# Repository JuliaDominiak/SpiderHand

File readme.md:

# SpiderHand: Supporting Arachnophobia Therapy UsingMotion-controlled Robotic Manipulator
Submitted to EAI Mobiquitous 2020

When attempting to set up the system for the first time, please consult short videos in Previews folder. It might be useful to understand the assembly details.

## Component list:
Below, we list all components necessary to successfully replicate SpiderHand manipulator. We encourage to introduce your own innovations and alter our design, yet at own risk.

**Microcontrollers and drivers**

- Adafruit Feather Huzzah ESP32   1 pcs.
- Adafruit Feather Huzzah ESP8266 5 pcs.
- ADS1015 12-Bit ADC - 4 Channel with Programmable Gain Amplifier 1 pcs.
- Adafruit 16-Channel 12-bit PWM/Servo Driver - I2C interface - PCA9685   2 pcs.

**Sensors, Servos, Devices**

- Flex Sensor 4.5"    1 pcs.
- Flex Sensor 2.2"    1 pcs.
- SparkFun Qwiic Flex Glove Controller    1 pcs.
- BendLabs 2-Axis Soft Flex Sensor    1 pcs.
- DFRobot 6 DOF Sensor - MPU6050  1 pcs.
- PowerHD HD-1501MG   3 pcs.
- PowerHD LF-20MG 1 pcs.
- Hitec HS-45HB   3 pcs.
- Shaftless Vibration Motor 10x3.4mm  5 pcs.

**Assembly Screws and Accessories**

- M2 nut  8 pcs.
- M2x8mm  11 pcs.
- M2x3mm  5 pcs.
- M3 nut  22 pcs.
- M3x6mm  8 pcs.
- M3x10mm 25 pcs.
- M3x18mm 4 pcs.
- M4 nut  2 pcs.
- M4x30mm 2 pcs.
- Aluminium horn - 20mm / 6mm 4 pcs.
- Servo extension 90cm    7 pcs.
- FeatherWing Proto - Prototyping Add-on  1 pcs.
- 10-wire Ribbon cable    5 m

**Fabric Accessories**

- Sport gloves    2 pcs.
- Elbow protector 1 pcs.
- Polyester tape (width: 2cm) 2m
- Buckles compatible with the 2cm tape    2 pcs.
- Latches 5mm 6 pcs.
- Latches 15mm    6 pcs.

## 3D printing remarks:

**Filaments used:**

1. Fiberlogy Easy PLA
2. Zortrax Z-ABS
3. Proto-paste Electrically Conductive Composite PLA
4. Fiberlogy Fiberflex 40D

**Printers used:**

1. Creality3D Ender-3
2. Zortrax M200

**Slicer:** Ultimaker Cura 4.5

Finger elements (Finger i Touch) and joints (Flex) should be reduced to 80% before printing because the elements come from the following project [https://www.thingiverse.com/thing:242639](https://www.thingiverse.com/thing:242639).

The elements from part_1 to part_10 and all the elements starting with “Finger” can be printed at your discretion using ABS or PLA. The important thing during printing is to set the lowest fill factor (in our case it is 12%) in order to relieve the construction.

The elements called “Flex” should be printed from the elastic material according to the manufacturer’s recommendations. It is suggested to use ironing on the last layer to obtain a consistent element.

The finger pads called “Touch” should be printed from the conductive material.

Before assembling according to the model, the following be embedded by heat-set insert (soldering nuts): M4: 1,2; M3: 8, 9, 24, 25, 26; M2: 1, 2, 3, 4, 5, 6, 7, 8, 12, 13

## Software remarks:

Source codes and drivers for the prototype are compatible with the Arduino IDE 1.8.12

It is necessary to install boards drivers:

1. esp32 by Espressif Systems version 1.0.2 [https://dl.espressif.com/dl/package_esp32_index.json](https://dl.espressif.com/dl/package_esp32_index.json)
2. esp8266 by ESP8266 Community version 2.1.0 [http://arduino.esp8266.com/stable/package_esp8266com_index.json](http://arduino.esp8266.com/stable/package_esp8266com_index.json)

<ins>Sensor and communication libraries used:</ins>

1. SparkFun_ADS1015_Arduino_Library
2. Adafruit_PWM_Servo_Driver_Library
3. ads_two_axis_driver
4. MPU6050
5. Adafruit_ADS1X15

**Sensor Calibration Sheet**

Auxiliary material contains a spreadsheet useful for calibrating the setup. Coefficient values for flex sensor calibration can be obtained using the Calibration.xlsx file. Please consult it for instruction on how to provide correct coefficient values to the MotorFingersElbow.ino source file.

**PCB Design**

The PCB boards were designed in EAGLE software (version 9.2.2).

## Controller assembly remarks:

Electronic components have to be sewn to the material elements.
The belt (thickness: 2cm) should be adjusted and ended with the buckles. In the middle part one shall sew one latch for each part. The other end will be attached to the sensors.

On the elbow protector 2 pairs of the 15mm latches should be attached, which will properly keep the loop and the beginning of the sensor.

Six small latches should be sewn to the glove - 5 to each vibration motor and 1 to the end of the 2-axis sensor. The remaining two bigger latches are to attach bend sensors on the fingers. In order to make the reading possible a second glove should be worn. The second option is to cut only the fingers.

Hope you’re enjoying SpiderHand!

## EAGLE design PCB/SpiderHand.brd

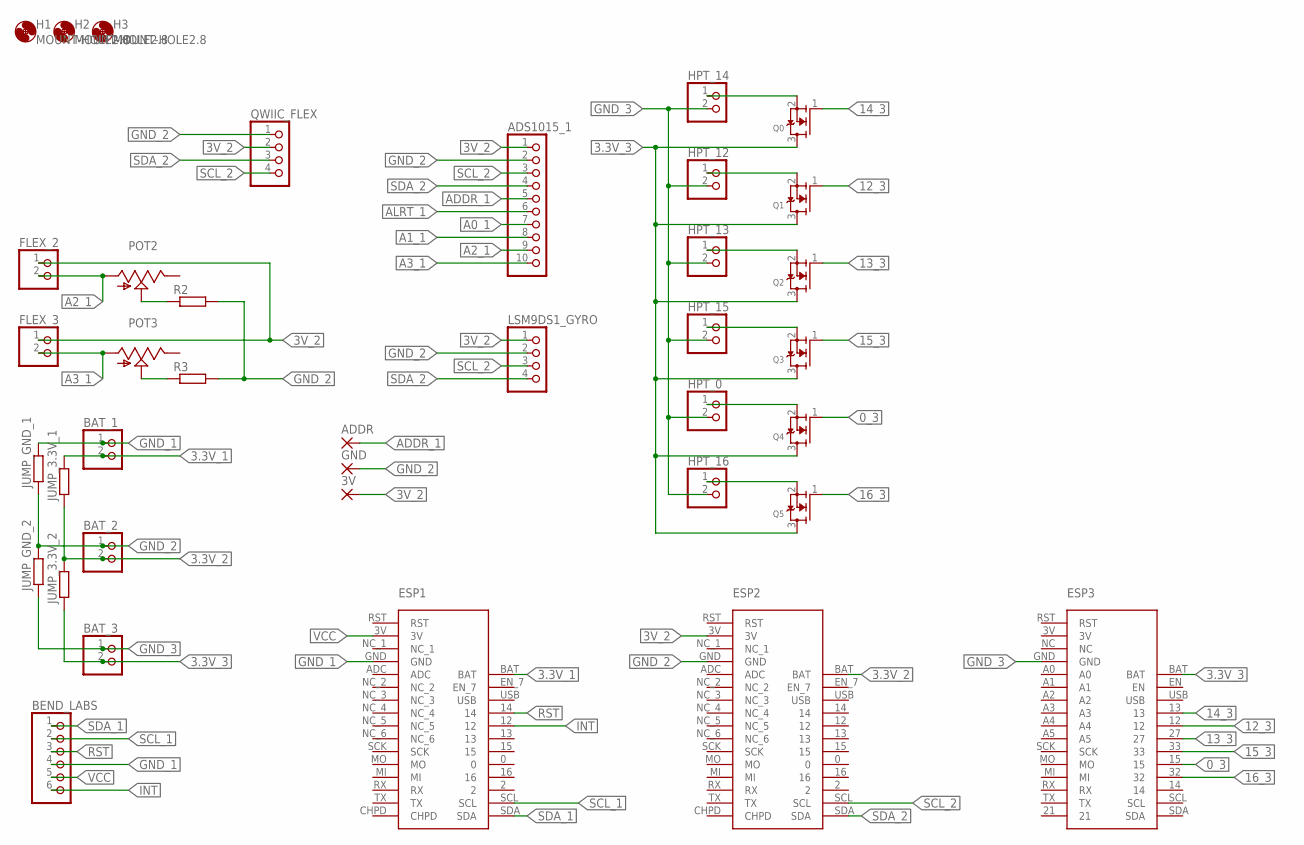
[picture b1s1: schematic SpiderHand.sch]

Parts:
3V: SMD2; SMD1,27-2,54
ADDR: SMD2; SMD1,27-2,54
ADS1015_1: PINHD-1X10; 1X10
BAT_1, BAT_2, BAT_3: PINHD-1X2; 1X02
BEND_LABS: PINHD-1X6/90; 1X06/90
ESP1, ESP2: ESP_8266_ADAFRUIT
ESP3: ESP_32_ADAFRUIT
FLEX_2, FLEX_3: PINHD-1X2; 1X02
GND: SMD2; SMD1,27-2,54
H1, H2, H3: MOUNT-HOLE2.8; 2,8
HPT_0, HPT_12, HPT_13, HPT_14, HPT_15, HPT_16: PINHD-1X2; 1X02
JUMP_3.3V_1, JUMP_3.3V_2: R-EU_M0805; M0805
JUMP_GND_1, JUMP_GND_2: R-EU_M0805; M0805
LSM9DS1_GYRO: PINHD-1X4/90; 1X04/90
POT2, POT3: TRIM_US-CA6V; CA6V
Q0, Q1, Q2, Q3, Q4, Q5: MOSFET-NREFLOW; SOT23
QWIIC_FLEX: PINHD-1X4/90; 1X04/90
R2, R3: R-EU_0204/7; 0204/7

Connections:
0_3: ESP3.15, Q4.1 (G)
3.3V_1: BAT_1.2, ESP1.BAT, JUMP_3.3V_1.2
3.3V_2: BAT_2.2, ESP2.BAT, JUMP_3.3V_1.1, JUMP_3.3V_2.2
3.3V_3: BAT_3.2, ESP3.BAT, JUMP_3.3V_2.1, Q0.3 (D), Q1.3 (D), Q2.3 (D), Q3.3 (D), Q4.3 (D), Q5.3 (D)
3V_2: 3V.1, ADS1015_1.1, ESP2.3V, FLEX_2.1, FLEX_3.1, LSM9DS1_GYRO.1, QWIIC_FLEX.2
12_3: ESP3.12, Q1.1 (G)
13_3: ESP3.27, Q2.1 (G)
14_3: ESP3.13, Q0.1 (G)
15_3: ESP3.33, Q3.1 (G)
16_3: ESP3.32, Q5.1 (G)
A0_1: ADS1015_1.7
A1_1: ADS1015_1.8
A2_1: ADS1015_1.9, FLEX_2.2, POT2.A
A3_1: ADS1015_1.10, FLEX_3.2, POT3.A
ADDR_1: ADDR.1, ADS1015_1.5
ALRT_1: ADS1015_1.6
GND_1: BAT_1.1, BEND_LABS.4, ESP1.GND, JUMP_GND_1.2
GND_2: ADS1015_1.2, BAT_2.1, ESP2.GND, GND.1, JUMP_GND_1.1, JUMP_GND_2.2, LSM9DS1_GYRO.2, QWIIC_FLEX.1, R2.2, R3.2
GND_3: BAT_3.1, ESP3.GND, HPT_0.2, HPT_12.2, HPT_13.2, HPT_14.2, HPT_15.2, HPT_16.2, JUMP_GND_2.1
INT: BEND_LABS.6, ESP1.12
unnamed: HPT_14.1, Q0.2 (S)
unnamed: HPT_12.1, Q1.2 (S)
unnamed: HPT_13.1, Q2.2 (S)
unnamed: HPT_15.1, Q3.2 (S)
unnamed: HPT_0.1, Q4.2 (S)
unnamed: HPT_16.1, Q5.2 (S)
unnamed: POT2.S, R2.1
unnamed: POT3.S, R3.1
RST: BEND_LABS.3, ESP1.14
SCL_1: BEND_LABS.2, ESP1.SCL
SCL_2: ADS1015_1.3, ESP2.SCL, LSM9DS1_GYRO.3, QWIIC_FLEX.4
SDA_1: BEND_LABS.1, ESP1.SDA
SDA_2: ADS1015_1.4, ESP2.SDA, LSM9DS1_GYRO.4, QWIIC_FLEX.3
VCC: BEND_LABS.5, ESP1.3V

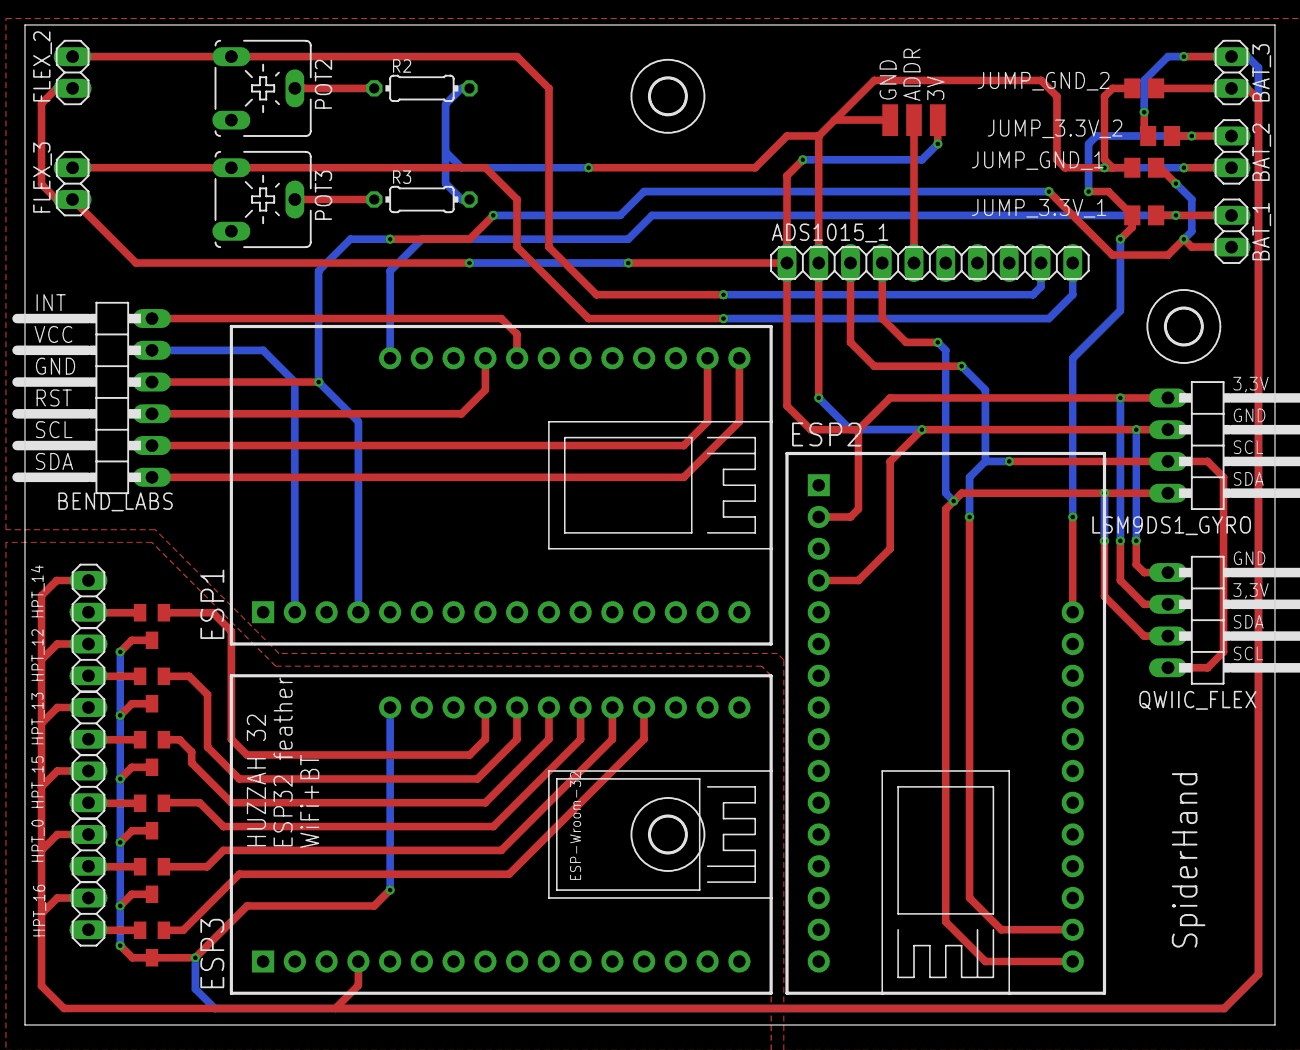
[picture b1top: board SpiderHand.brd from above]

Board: 2 copper layers, 100.0 x 80.0 mm, 38 parts (0 on the bottom side), 31 nets.

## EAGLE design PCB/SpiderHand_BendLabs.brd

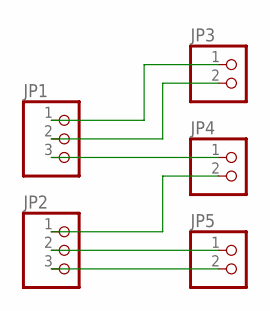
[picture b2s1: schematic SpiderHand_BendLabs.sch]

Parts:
JP1, JP2: PINHD-1X3; 1X03
JP3, JP4, JP5: PINHD-1X2; 1X02

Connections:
GND: JP2.1, JP4.2
INT: JP2.3, JP5.2
RST: JP1.3, JP4.1
SCL: JP1.2, JP3.2
SDA: JP1.1, JP3.1
VCC: JP2.2, JP5.1

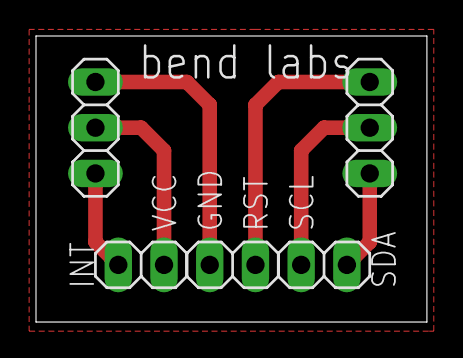
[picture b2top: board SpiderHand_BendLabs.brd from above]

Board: 2 copper layers, 21.7 x 15.9 mm, 5 parts (0 on the bottom side), 6 nets.

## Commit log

2023-02-20 hopefully the images will be displayed correctly
2023-02-20 basics
2023-02-22 sends over udp
2023-02-22 rawer over udp, member callback function in gauntlet
2023-02-23 dmp sucks
2023-02-23 mpu basic readout
2023-04-01 it builds with gyro *shrug*, will check if it works later
2023-05-06 disable gyro, add calibration
2023-05-14 hand udp conn, parsing commands to servos
2023-05-14 range setup
2023-05-17 robohand done, (some unnecessary debug prints left)
2023-05-17 remove unused var, hopefully this still works
2023-05-31 it's a piece of crap but it works
2023-06-13 calibrated
2023-06-20 stuff
2023-06-20 refactored
2023-06-25 cppcheck
2023-06-26 elbow works
2023-06-26 filter
2023-06-26 filter cast operator
2023-06-26 reenable other joints
2023-07-12 filter define, elbow callibration
2023-07-12 change elbow channel
2023-11-24 new filter v1
2023-11-25 fix new filter
2023-11-28 some fixes
2023-11-28 some more fixes
